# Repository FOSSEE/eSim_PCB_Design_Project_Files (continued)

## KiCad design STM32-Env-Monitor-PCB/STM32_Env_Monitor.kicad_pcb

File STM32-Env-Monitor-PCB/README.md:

# STM32-Based Smart Environmental Monitoring and Control PCB

## Overview

This project is an STM32-based four-layer PCB designed for **smart environmental monitoring and control in aquaculture systems**. The board integrates the microcontroller, environmental sensor interfaces, power management, communication interfaces, and control circuitry required for monitoring and managing aquaculture conditions.

## PCB Design

The board is designed as a **four-layer PCB** with the following stack-up:

* **Layer 1 (Top):** Components and signal routing
* **Layer 2:** Dedicated GND plane
* **Layer 3:** Dedicated +3.3 V power plane
* **Layer 4 (Bottom):** Components and signal routing

The four-layer stack-up provides dedicated power and ground planes while allowing organized signal routing and improved power distribution. Component placement and routing were planned to maintain clear separation between sensitive environmental sensing signals and higher-current control paths.

## Application

The PCB is intended for aquaculture applications where environmental parameters can be monitored and controlled to help maintain suitable conditions for aquatic organisms. The STM32-based system provides the processing and control required to interface with sensors and connected control devices.

## Documentation

For the complete circuit description, PCB layout, routing methodology, design considerations, DRC results, and 3D views, refer to the accompanying project report.

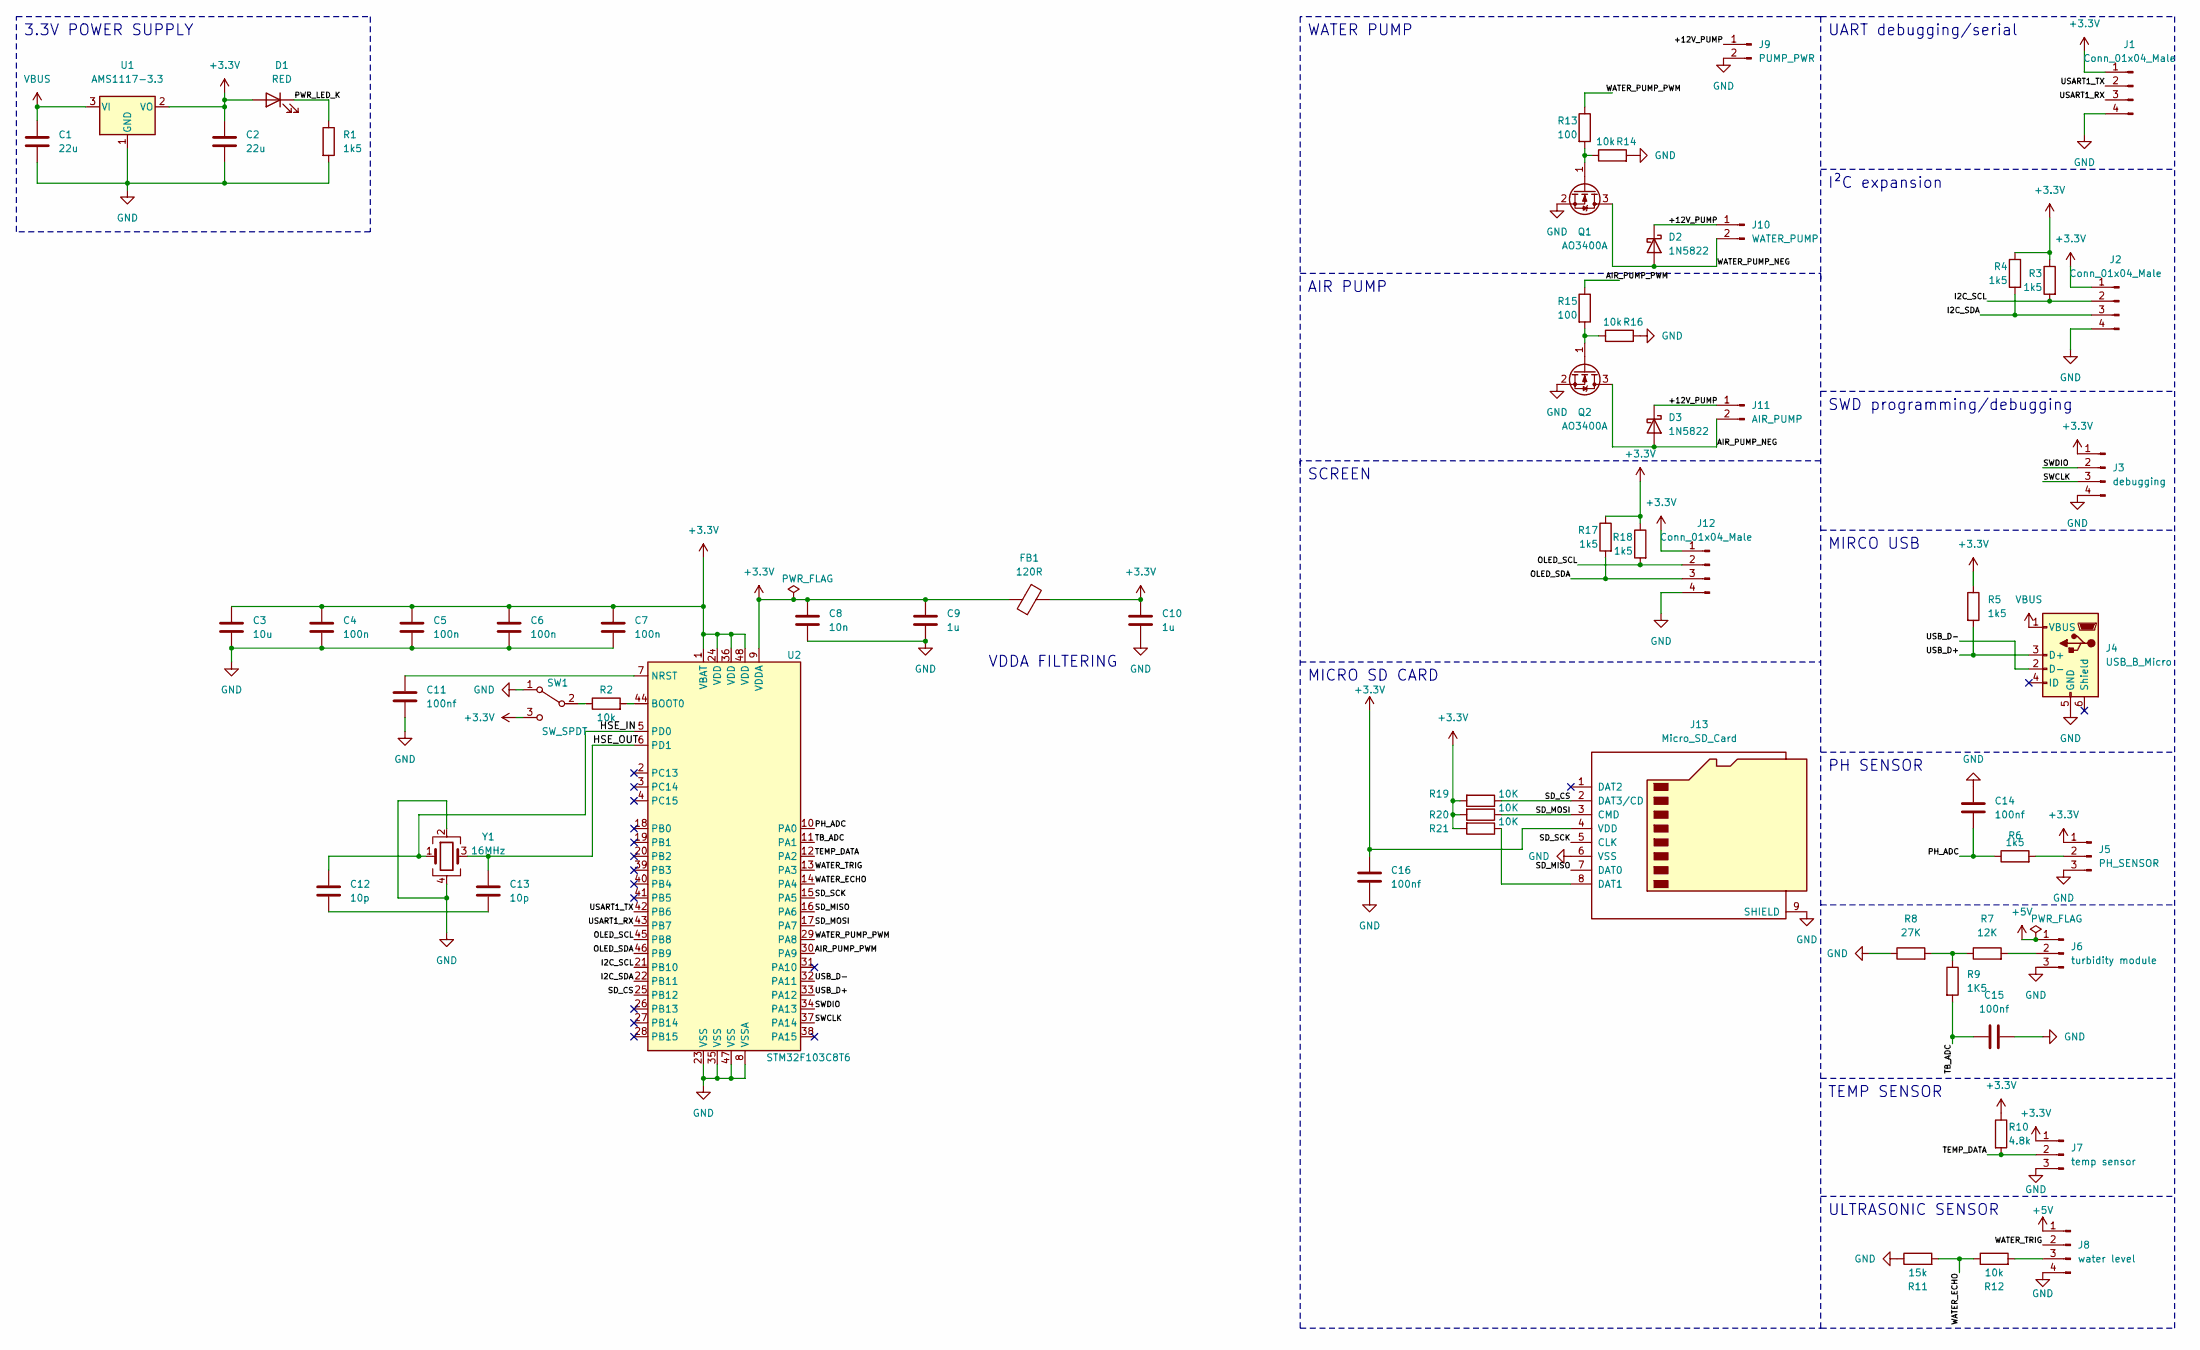
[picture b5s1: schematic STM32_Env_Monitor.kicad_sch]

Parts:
C1, C2: 22u; C_0805_2012Metric
C3: 10u; C_0603_1608Metric
C4, C5, C6, C7: 100n; C_0402_1005Metric_Pad0.74x0.62mm_HandSolder
C8: 10n; C_0402_1005Metric_Pad0.74x0.62mm_HandSolder
C9, C10: 1u; C_0402_1005Metric_Pad0.74x0.62mm_HandSolder
C11, C14, C15: 100nf; C_0402_1005Metric_Pad0.74x0.62mm_HandSolder
C12, C13: 10p; C_0402_1005Metric_Pad0.74x0.62mm_HandSolder
C16: 100nf; C_0402_1005Metric
D1: RED; LED_0603_1608Metric
D2, D3: 1N5822; D_DO-201AE_P3.81mm_Vertical_AnodeUp
FB1: 120R; L_0603_1608Metric
J1, J2, J12: Conn_01x04_Male; PinHeader_1x04_P2.54mm_Vertical
J3: debugging; PinHeader_1x04_P2.54mm_Vertical
J4: USB_B_Micro; USB_Micro-B_Wuerth_629105150521
J5: PH_SENSOR; PinHeader_1x03_P2.54mm_Vertical
J6: turbidity module; PinHeader_1x03_P2.54mm_Vertical
J7: temp sensor; PinHeader_1x03_P2.54mm_Vertical
J8: water level; PinHeader_1x04_P2.54mm_Vertical
J9: PUMP_PWR; PinHeader_1x02_P2.54mm_Vertical
J10: WATER_PUMP; PinHeader_1x02_P2.54mm_Vertical
J11: AIR_PUMP; PinHeader_1x02_P2.54mm_Vertical
J13: Micro_SD_Card; microSD_HC_Molex_47219-2001
Q1, Q2: AO3400A; SOT-23
R1, R3, R4, R5, R6, R17, R18: 1k5; R_0603_1608Metric
R2, R12, R14, R16: 10k; R_0603_1608Metric
R7: 12K; R_0603_1608Metric
R8: 27K; R_0603_1608Metric
R9: 1K5; R_0603_1608Metric
R10: 4.8k; R_0603_1608Metric
R11: 15k; R_0603_1608Metric
R13, R15: 100; R_0603_1608Metric
R19, R20, R21: 10K; R_0603_1608Metric
SW1: SW_SPDT; SW_SPDT_PCM12
U1: AMS1117-3.3; SOT-223-3_TabPin2
U2: STM32F103C8T6; LQFP-48_7x7mm_P0.5mm
Y1: 16MHz; Crystal_SMD_3225-4Pin_3.2x2.5mm

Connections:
+3.3V: C2.1, C3.1, C4.1, C5.1, C6.1, C7.1, C8.1, C9.1, C10.1, C16.1, D1.2 (A), FB1.1, FB1.2, J1.1, J2.1, J3.1, J5.1, J7.1, J12.1, J13.4 (VDD), R3.1, R4.1, R5.1, R10.1, R17.1, R18.1, R19.2, R20.2, R21.2, SW1.3 (C), U1.2 (VO), U2.1 (VBAT), U2.9 (VDDA), U2.24 (VDD), U2.36 (VDD), U2.48 (VDD)
+5V: J6.1, J8.1
/+12V_PUMP: D2.1 (K), D3.1 (K), J9.1, J10.1, J11.1
/AIR_PUMP_NEG: D3.2 (A), J11.2, Q2.3 (D)
/AIR_PUMP_PWM: R15.1, U2.30 (PA9)
/HSE_IN: C12.1, U2.5 (PD0), Y1.1
/HSE_OUT: C13.1, U2.6 (PD1), Y1.3
/I2C_SCL: J2.2, R3.2, U2.21 (PB10)
/I2C_SDA: J2.3, R4.2, U2.22 (PB11)
/OLED_SCL: J12.2, R18.2, U2.45 (PB8)
/OLED_SDA: J12.3, R17.2, U2.46 (PB9)
/PH_ADC: C14.2, R6.1, U2.10 (PA0)
/PWR_LED_K: D1.1 (K), R1.1
/SD_CS: J13.2 (DAT3/CD), R19.1, U2.25 (PB12)
/SD_MISO: J13.7 (DAT0), U2.16 (PA6)
/SD_MOSI: J13.3 (CMD), R20.1, U2.17 (PA7)
/SD_SCK: J13.5 (CLK), U2.15 (PA5)
/SWCLK: J3.3, U2.37 (PA14)
/SWDIO: J3.2, U2.34 (PA13)
/TB_ADC: C15.1, R9.2, U2.11 (PA1)
/TEMP_DATA: J7.2, R10.2, U2.12 (PA2)
/USART1_RX: J1.3, U2.43 (PB7)
/USART1_TX: J1.2, U2.42 (PB6)
/USB_D+: J4.3 (D+), R5.2, U2.33 (PA12)
/USB_D-: J4.2 (D-), U2.32 (PA11)
/WATER_ECHO: R11.2, R12.1, U2.14 (PA4)
/WATER_PUMP_NEG: D2.2 (A), J10.2, Q1.3 (D)
/WATER_PUMP_PWM: R13.1, U2.29 (PA8)
/WATER_TRIG: J8.2, U2.13 (PA3)
GND: C1.2, C2.2, C3.2, C4.2, C5.2, C6.2, C7.2, C8.2, C9.2, C10.2, C11.2, C14.1, C15.2, C16.2, J1.4, J2.4, J3.4, J4.5 (GND), J5.3, J6.3, J7.3, J8.4, J9.2, J12.4, J13.6 (VSS), J13.9 (SHIELD), Q1.2 (S), Q2.2 (S), R1.2, R8.1, R11.1, R14.2, R16.2, SW1.1 (A), U1.1 (GND), U2.8 (VSSA), U2.23 (VSS), U2.35 (VSS), U2.47 (VSS), Y1.2, Y1.4
unnamed: C12.2, C13.2
unnamed: J5.2, R6.2
unnamed: J6.2, R7.2
unnamed: J8.3, R12.2
unnamed: J13.8 (DAT1), R21.1
unnamed: Q1.1 (G), R13.2, R14.1
unnamed: Q2.1 (G), R15.2, R16.1
unnamed: R7.1, R8.2, R9.1
unnamed: R2.1, SW1.2 (B)
unnamed: R2.2, U2.44 (BOOT0)
unnamed: C11.1, U2.7 (NRST)
VBUS: C1.1, J4.1 (VBUS), U1.3 (VI)

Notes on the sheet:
MICRO SD CARD
I²C expansion
3.3V POWER SUPPLY
PH SENSOR
VDDA FILTERING
AIR PUMP
TEMP SENSOR
SWD programming/debugging
WATER PUMP
ULTRASONIC SENSOR
UART debugging/serial
MIRCO USB
SCREEN

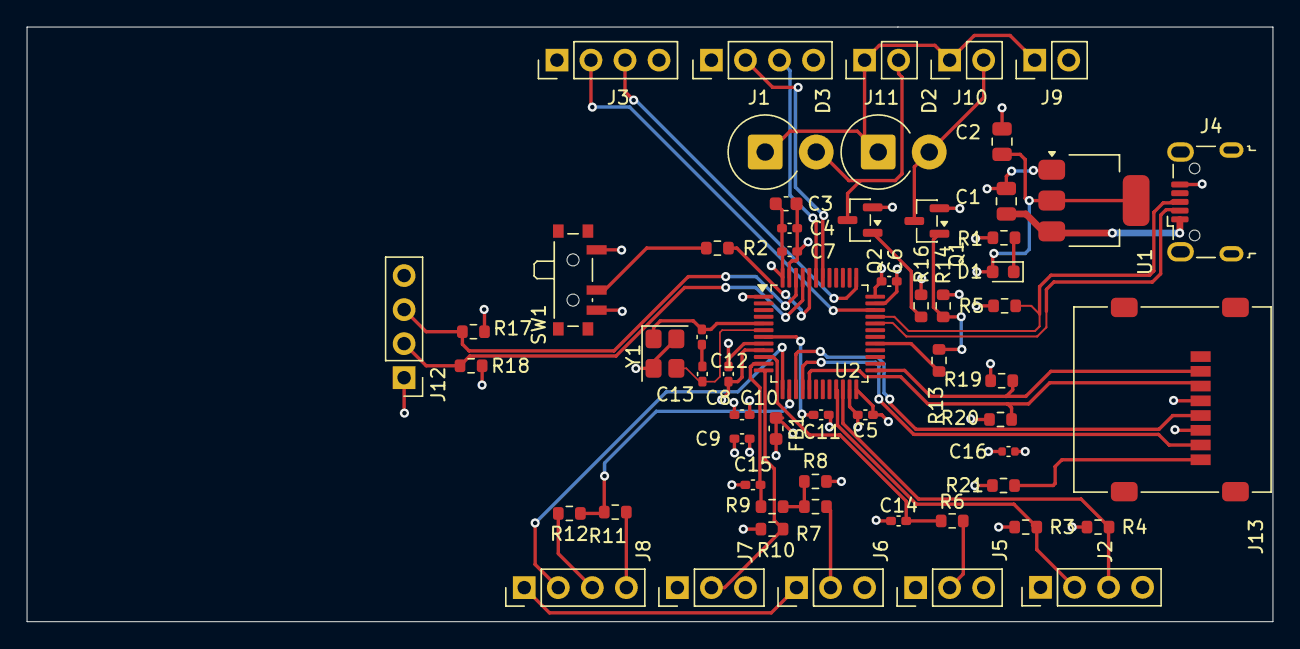
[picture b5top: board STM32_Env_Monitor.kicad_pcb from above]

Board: 4 copper layers, 93.0 x 44.4 mm, 59 parts (0 on the bottom side), 41 nets.

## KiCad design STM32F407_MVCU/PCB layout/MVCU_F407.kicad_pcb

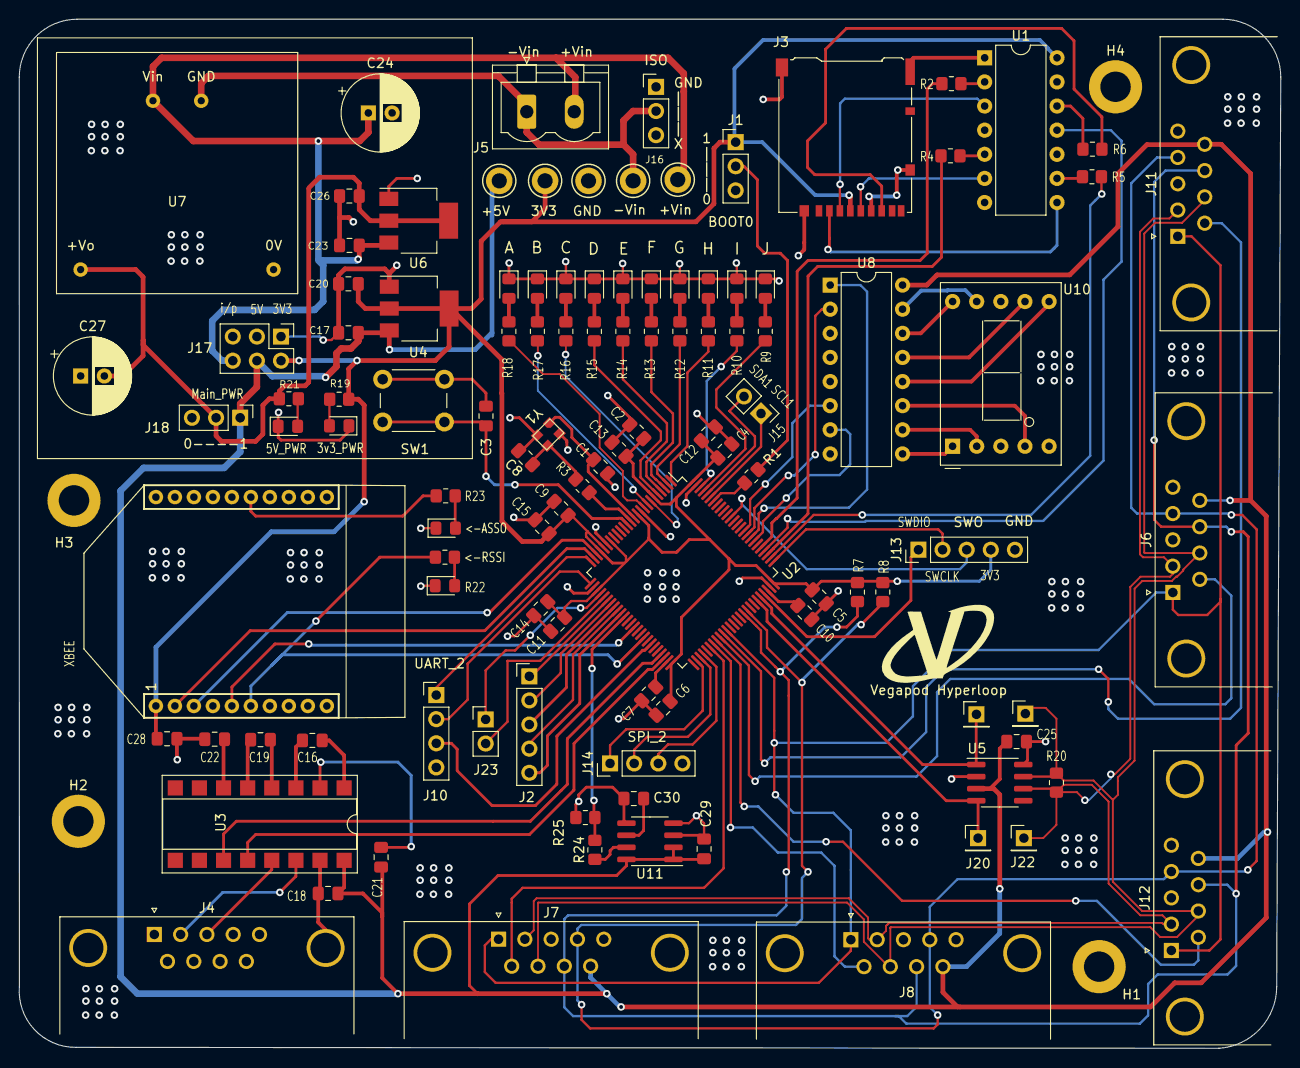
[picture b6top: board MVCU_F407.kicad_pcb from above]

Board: 4 copper layers, 132.8 x 108.4 mm, 113 parts (0 on the bottom side), 109 nets.

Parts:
3V3: TestPoint; TestPoint_Keystone_5010-5014_Multipurpose
+5V: TestPoint; TestPoint_Keystone_5010-5014_Multipurpose
+Vin: TestPoint; TestPoint_Keystone_5010-5014_Multipurpose
-Vin: TestPoint; TestPoint_Keystone_5010-5014_Multipurpose
C1, C8: 12p; C_0805_2012Metric_Pad1.18x1.45mm_HandSolder
C2, C17, C20, C23, C26, C29, C30: 10uF; C_0805_2012Metric_Pad1.18x1.45mm_HandSolder
C3, C4, C5, C6, C9, C11, C12, C13, C14: 100nF; C_0805_2012Metric_Pad1.18x1.45mm_HandSolder
C7, C10: 2.2uF; C_0805_2012Metric_Pad1.18x1.45mm_HandSolder
C15, C25: 1uF; C_0805_2012Metric_Pad1.18x1.45mm_HandSolder
C16, C18, C19, C21, C22, C28: 0.1uF; C_0805_2012Metric_Pad1.18x1.45mm_HandSolder
C24: 100uF; CP_Radial_D8.0mm_P2.50mm
C27: 10uF; CP_Radial_D8.0mm_P2.50mm
D1, D2, D3, D4, D5, D6, D7, D8, D9, D10, D11, D12, D13, D14: LED; LED_0805_2012Metric_Pad1.15x1.40mm_HandSolder
GND: TestPoint; TestPoint_Keystone_5010-5014_Multipurpose
H1, H2, H3, H4: MountingHole_Pad; MountingHole_3.2mm_M3_DIN965_Pad
J1, J16, J18: Conn_01x03_Male; PinHeader_1x03_P2.54mm_Vertical
J2: Conn_01x05_Male; PinHeader_1x05_P2.54mm_Vertical
J3: Micro_SD_Card_Det_Hirose_DM3AT; microSD_HC_Hirose_DM3AT-SF-PEJM5
J4: IMU; DSUB-9_Male_Horizontal_P2.77x2.84mm_EdgePinOffset7.70mm_Hou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
J5: Conn_01x02_Male; PhoenixContact_MSTBVA_2,5_2-G_1x02_P5.00mm_Vertical
J6, J7, J8, J11, J12: DB9_Male_MountingHoles; DSUB-9_Male_Horizontal_P2.77x2.84mm_EdgePinOffset7.70mm_Hou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
J10, J14: Uart; PinHeader_1x04_P2.54mm_Vertical
J13: SWD; PinHeader_1x05_P2.54mm_Vertical
J15, J23: Conn_01x02_Male; PinHeader_1x02_P2.54mm_Vertical
J17: Conn_02x03_Counter_Clockwise; PinHeader_2x03_P2.54mm_Vertical
J19, J20, J21, J22: Conn_01x01_Male; PinHeader_1x01_P2.54mm_Vertical
R1: 10K; R_0805_2012Metric_Pad1.20x1.40mm_HandSolder
R2, R4, R5, R6: 3.3k; R_0805_2012Metric_Pad1.20x1.40mm_HandSolder
R3: R_Small_US; R_0805_2012Metric_Pad1.20x1.40mm_HandSolder
R7, R8, R9, R10, R11, R12, R13, R14, R15, R16, R17, R18, R19, R21, R22, R23: 1K; R_0805_2012Metric_Pad1.20x1.40mm_HandSolder
R20: 120R; R_0805_2012Metric_Pad1.20x1.40mm_HandSolder
R24, R25: 1.5k; R_0805_2012Metric_Pad1.20x1.40mm_HandSolder
SW1: SW_Push; SW_PUSH_6mm_H5mm
U1: 74LS125; DIP-14_W7.62mm
U2: STM32F407VGTx; LQFP-100_14x14mm_P0.5mm
U3: MAX232; DIP-16_W7.62mm_SMDSocket_SmallPads
U4: AMS1117-3.3; SOT-223-3_TabPin2
U5: MCP2551-I-SN; SOIC-8_3.9x4.9mm_P1.27mm
U6: AMS1117-5.0; SOT-223-3_TabPin2
U7: MORNSUN-URB2405YMD-6WR3
U8: 74LS47; DIP-16_W7.62mm
U9: XB24CDMPIT-001; XBEE
U10: D168K; D1X8K
U11: ACS712xLCTR-20A; SOIC-8_3.9x4.9mm_P1.27mm
Y1: Crystal_GND24; crystal

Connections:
+3.3V: 3V3.1, C2.1, C4.1, C5.1, C6.1, C9.1, C11.1, C12.1, C13.1, C14.1, C15.1, C20.1, C28.1, J1.1, J3.4 (VDD), J13.4, J17.2, R7.1, R8.1, R19.2, U1.14 (VCC), U2.6 (VBAT), U2.11 (VDD), U2.19 (VDD), U2.21 (VREF+), U2.22 (VDDA), U2.28 (VDD), U2.50 (VDD), U2.75 (VDD), U2.100 (VDD), U4.2 (VO), U9.1
+5V: +5V.1, C17.1, C18.1, C21.1, C25.1, C29.1, J6.9, J7.9, J8.9, J11.9, J12.9, J17.4, J18.1, U3.16 (VCC), U4.3 (VI), U5.3 (VDD), U8.16 (VCC), U11.1 (IP+), U11.2 (IP+), U11.8 (VCC)
/ADC_in6: J2.1, U2.31 (PA6)
/ADC_in7: J2.2, U2.32 (PA7)
/ADC_in8: J2.5, U2.35 (PB0)
/ADC_in9: R24.2, R25.1, U2.36 (PB1)
/ADC_in14: J2.3, U2.33 (PC4)
/ADC_in15: J2.4, U2.34 (PC5)
/BOOT0: R1.2, U2.94 (BOOT0)
/C13: R16.2, U2.7 (PC13)
/C14: R17.2, U2.8 (PC14)
/C15: R18.2, U2.9 (PC15)
/CAN_N: J6.2, J7.2, J8.2, J11.2, J12.2, J22.1, R20.2, U5.6 (CANL)
/CAN_P: J6.7, J7.7, J8.7, J11.7, J12.7, J21.1, R20.1, U5.7 (CANH)
/CAN_Rx: J20.1, U2.70 (PA11), U5.4 (RXD)
/CAN_Tx: J19.1, U2.71 (PA12), U5.1 (TXD)
/CS_LLS: J3.2 (DAT3/CD), U1.8
/DAC_1: J23.1, U2.29 (PA4)
/DAC_2: J23.2, U2.30 (PA5)
/DI_LLS: J3.3 (CMD), U1.3
/DO_LLS: J3.7 (DAT0), R6.2
/E0: R9.2, U2.97 (PE0)
/E1: R10.2, U2.98 (PE1)
/E2: R11.2, U2.1 (PE2)
/E3: R12.2, U2.2 (PE3)
/E4: R13.2, U2.3 (PE4)
/E5: R14.2, U2.4 (PE5)
/E6: R15.2, U2.5 (PE6)
/HSE_IN: C1.2, U2.12 (PH0), Y1.1
/HSE_OUT: R3.1, U2.13 (PH1)
/I2C1_SCL: J15.1, U2.95 (PB8)
/I2C1_SDA: J15.2, U2.96 (PB9)
/I2C3_SCL: J6.4, J7.4, J8.4, J11.4, J12.4, R8.2, U2.67 (PA8)
/I2C_SDA: J6.8, J7.8, J8.8, J11.8, J12.8, R7.2, U2.66 (PC9)
/IMU_Rx: U2.48 (PB11), U3.12 (R1OUT)
/IMU_Tx: U2.47 (PB10), U3.11 (T1IN)
/MVCU_HBT: J6.1, J7.1, J8.1, J11.1, J12.1, U2.61 (PD14)
/RSSI: R22.2, U2.42 (PE11), U9.6
/RST: U2.39 (PE8), U9.5
/Rx: J4.2, U3.14 (T1OUT)
/SCK_LLS: J3.5 (CLK), U1.6
/SD_CS: R5.2, U2.77 (PA15)
/SD_MISO: U1.11, U2.79 (PC11)
/SD_MOSI: R2.2, U2.80 (PC12)
/SD_SCK: R4.2, U2.78 (PC10)
/SPI2_MISO: J14.2, U2.53 (PB14)
/SPI2_MOSI: J14.3, U2.54 (PB15)
/SPI2_SCK: J14.1, U2.52 (PB13)
/SWCLK: J13.2, U2.76 (PA14)
/SWDIO: J13.1, U2.72 (PA13)
/SWo: J13.3, U2.89 (PB3)
/Tx: J4.3, U3.13 (R1IN)
/USART2_Rx: J10.2, U2.26 (PA3)
/USART2_Tx: J10.1, U2.25 (PA2)
/VCU1_HBT: J11.6, U2.60 (PD13)
/VCU2_HBT: J6.6, U2.59 (PD12)
/VCU3_HBT: J12.6, U2.58 (PD11)
/VCU4_HBT: J8.6, U2.57 (PD10)
/VCU5_HBT: J7.6, U2.56 (PD9)
/Xbee_Rx: U2.23 (PA0), U9.3
/Xbee_Tx: U2.24 (PA1), U9.2
/display_a: U2.82 (PD1), U8.7 (A)
/display_b: U2.83 (PD2), U8.1 (B)
/display_c: U2.84 (PD3), U8.2 (C)
/display_d: U2.85 (PD4), U8.6 (D)
/gpio: J10.3, U2.44 (PE13)
/mornsun_Vin: +Vin.1, C23.1, C24.1, J5.2, J17.6, U6.3 (VI), U7.2 (Vin)
/mornsun_minus: -Vin.1, J5.1, J16.2, U7.1 (GND)
GND: C1.1, C2.2, C3.2, C4.2, C5.2, C6.2, C7.1, C8.1, C9.2, C10.1, C11.2, C12.2, C13.2, C14.2, C15.2, C17.2, C18.2, C20.2, C22.1, C23.2, C24.2, C25.2, C26.2, C27.1, C28.2, C29.2, C30.2, D1.1 (K), D2.1 (K), D3.1 (K), D4.1 (K), D5.1 (K), D6.1 (K), D7.1 (K), D8.1 (K), D9.1 (K), D10.1 (K), D11.1 (K), D12.1 (K), D13.1 (K), D14.1 (K), GND.1, H1.1, H2.1, H3.1, H4.1, J1.3, J3.6 (VSS), J3.11 (SHIELD), J4.0 (PAD), J4.5, J6.0 (PAD), J6.3, J6.5, J7.0 (PAD), J7.3, J7.5, J8.0 (PAD), J8.3, J8.5, J10.4, J11.0 (PAD), J11.3, J11.5, J12.0 (PAD), J12.3, J12.5, J13.5, J14.4, J16.1, J17.1, J17.3, J17.5, R25.2, SW1.1, U1.1, U1.4, U1.7 (GND), U1.10, U1.13, U2.10 (VSS), U2.20 (VSSA), U2.27 (VSS), U2.74 (VSS), U2.99 (VSS), U3.15 (GND), U4.1 (GND), U5.2 (VSS), U5.8 (Rs), U6.1 (GND), U7.4 (0V), U8.8 (GND), U9.10, U10.3 (CC), U10.8 (CC), U11.3 (IP-), U11.4 (IP-), U11.5 (GND), Y1.2, Y1.4
unnamed: C3.1, SW1.2, U2.14 (NRST)
unnamed: C7.2, U2.49 (VCAP_1)
unnamed: C8.2, R3.2, Y1.3
unnamed: C10.2, U2.73 (VCAP_2)
unnamed: C16.1, U3.3 (C1-)
unnamed: C16.2, U3.1 (C1+)
unnamed: C19.1, U3.5 (C2-)
unnamed: C19.2, U3.4 (C2+)
unnamed: C21.2, U3.2 (VS+)
unnamed: C22.2, U3.6 (VS-)
unnamed: C26.1, C27.2, J18.2, R21.2, U6.2 (VO), U7.3 (+Vo)
unnamed: C30.1, U11.6 (FILTER)
unnamed: D1.2 (A), R9.1
unnamed: D2.2 (A), R10.1
unnamed: D3.2 (A), R11.1
unnamed: D4.2 (A), R12.1
unnamed: D5.2 (A), R13.1
unnamed: D6.2 (A), R14.1
unnamed: D7.2 (A), R15.1
unnamed: D8.2 (A), R16.1
unnamed: D9.2 (A), R17.1
unnamed: D10.2 (A), R18.1
unnamed: D11.2 (A), R19.1
unnamed: D12.2 (A), R21.1
unnamed: D13.2 (A), R22.1
unnamed: D14.2 (A), R23.1
unnamed: J1.2, R1.1
unnamed: R2.1, U1.2
unnamed: R4.1, U1.5
unnamed: R5.1, U1.9
unnamed: R6.1, U1.12
unnamed: R23.2, U9.15
unnamed: R24.1, U11.7 (VIOUT)
unnamed: U8.9 (e), U10.1 (E)
unnamed: U8.10 (d), U10.2 (D)
unnamed: U8.11 (c), U10.4 (C)
unnamed: U8.12 (b), U10.6 (B)
unnamed: U8.13 (a), U10.7 (A)
unnamed: U8.15 (f), U10.9 (F)
unnamed: U8.14 (g), U10.10 (G)

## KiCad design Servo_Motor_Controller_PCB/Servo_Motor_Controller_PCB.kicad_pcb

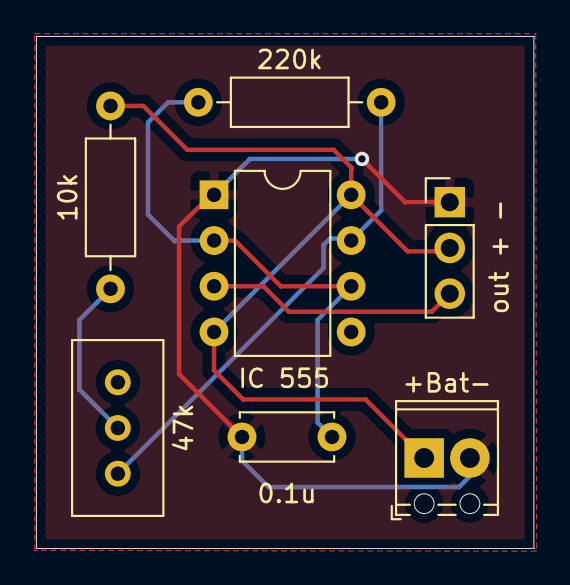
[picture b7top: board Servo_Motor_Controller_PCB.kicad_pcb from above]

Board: 2 copper layers, 27.6 x 28.4 mm, 7 parts (0 on the bottom side), 6 nets.

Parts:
0.1u: 0.1u; C_Disc_D5.0mm_W2.5mm_P5.00mm
10k: 10k; R_Axial_DIN0207_L6.3mm_D2.5mm_P10.16mm_Horizontal
47k: 47k; Potentiometer_Bourns_3296W_Vertical
220k: 220k; R_Axial_DIN0207_L6.3mm_D2.5mm_P10.16mm_Horizontal
+Bat-: BAT; TerminalBlock_Phoenix_MPT-0,5-2-2.54_1x02_P2.54mm_Horizontal
IC 555: LM555N; DIP-8_W7.62mm
out + -: eSim_3PinConn; PinHeader_1x03_P2.54mm_Vertical

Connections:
/DISC: 47k.1, 220k.2, IC 555.7 (DIS)
/OUT: IC 555.3 (Q), out + -.3
/R_OUT: 10k.1, 47k.2
/TR: 0.1u.1, 220k.1, IC 555.2 (TR), IC 555.6 (THR)
GND: 0.1u.2, +Bat-.2, IC 555.1 (GND), out + -.1
VCC: 10k.2, +Bat-.1, IC 555.4 (R), IC 555.8 (VCC), out + -.2

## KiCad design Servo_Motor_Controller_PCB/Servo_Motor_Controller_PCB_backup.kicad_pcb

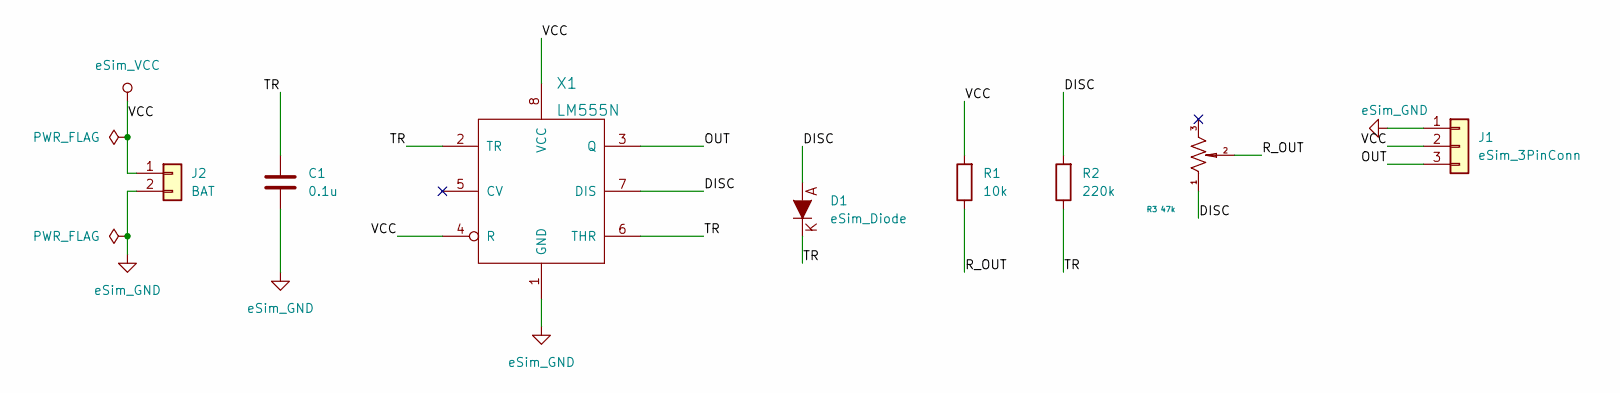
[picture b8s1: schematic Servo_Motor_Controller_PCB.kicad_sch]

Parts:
C1: 0.1u; C_Disc_D5.0mm_W2.5mm_P5.00mm
D1: eSim_Diode; D_DO-41_SOD81_P10.16mm_Horizontal
J1: eSim_3PinConn; PinHeader_1x03_P2.54mm_Vertical
J2: BAT; TerminalBlock_Phoenix_MPT-0,5-2-2.54_1x02_P2.54mm_Horizontal
R1: 10k; R_Axial_DIN0207_L6.3mm_D2.5mm_P10.16mm_Horizontal
R2: 220k; R_Axial_DIN0207_L6.3mm_D2.5mm_P10.16mm_Horizontal
R3: 47k; Potentiometer_Bourns_3296W_Vertical
X1: LM555N; DIP-8_W7.62mm

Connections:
/DISC: D1.1 (A), R2.2, R3.1, X1.7 (DIS)
/OUT: J1.3, X1.3 (Q)
/R_OUT: R1.1, R3.2
/TR: C1.1, D1.2 (K), R2.1, X1.2 (TR), X1.6 (THR)
GND: C1.2, J1.1, J2.2, X1.1 (GND)
VCC: J1.2, J2.1, R1.2, X1.4 (R), X1.8 (VCC)

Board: 2 copper layers, 8 parts (0 on the bottom side), 6 nets, no tracks yet.
